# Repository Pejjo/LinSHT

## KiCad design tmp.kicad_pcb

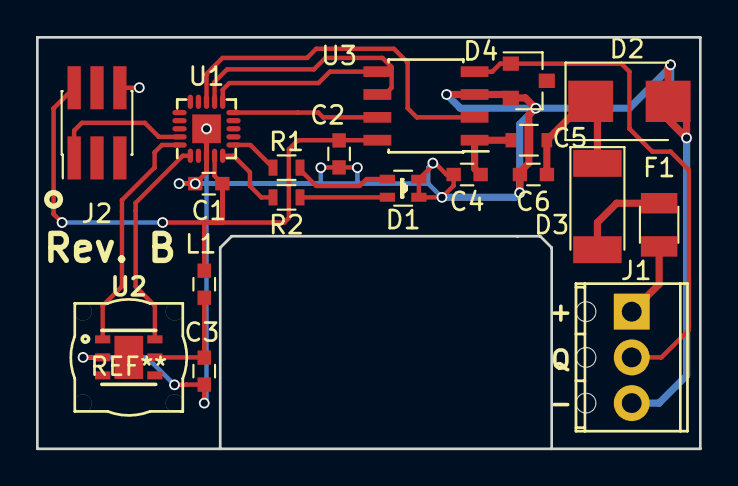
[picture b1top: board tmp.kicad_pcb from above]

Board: 2 copper layers, 36.8 x 22.9 mm, 19 parts (0 on the bottom side), 19 nets.

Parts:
C1: C; C_0603
C2, C3, C4: 100n; C_0603
C5: 1000p 50V .4A; C_0805_3
C6: 2u2; C_0603
D1: LED_Dual_ACAC; Dual_Led_0605
D2: SMBJ28A; D_SMB
D3: LL4001; D_MELF
D4: NUP1105LT1G; SOT-23
F1: 125mA; Fuse_SMD1206_Reflow
J1: Screw_Terminal_1x03; TerminalBlock_Pheonix_MPT-2.54mm_3pol
J2: CONN_02X03; Pin_Header_Straight_2x03_Pitch1.27mm_SMD
L1: 600Ohm; C_0603
R1, R2: 1k; R_0603
U1: ATTINY816-MFR; UQFN-20-1EP_3x3mm_Pitch0.45mm
U2: SHT2x; SON100P300X300X110-7N
U3: TJA1028TK; SOIC-8_3.9x4.9mm_Pitch1.27mm

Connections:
+3V3: C1.1, C2.1, J2.2, L1.1, U1.4, U3.8
GND: C1.2, C2.2, C3.2, C4.2, C5.2, C6.2, D1.2, D1.4, D2.2, D4.2, J1.3, J2.6, U1.3, U1.21, U2.2, U3.3
unnamed: C3.1, L1.2, U2.5
unnamed: C4.1, C5.1, U3.1
unnamed: C5.3, C6.1, D2.1, D3.1
unnamed: D1.1, R2.2
unnamed: D1.3, R1.2
unnamed: D3.2, F1.2
unnamed: D4.1, J1.2, U3.4
unnamed: F1.1, J1.1
unnamed: J2.1, U1.19
unnamed: R1.1, U1.6
unnamed: R2.1, U1.5
unnamed: U1.1, U2.6
unnamed: U1.10, U3.7
unnamed: U1.11, U3.5
unnamed: U1.12, U3.6
unnamed: U1.13, U3.2
unnamed: U1.20, U2.1
